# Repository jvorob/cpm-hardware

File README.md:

# cpm-hardware

This repo contains the design files for the custom PCB used in my Cathodic Protection Monitoring project.
These were developed in KiCad 8.
(see [main repo](https://github.com/jvorob/cpm-firmware) for more details)

`cpm_proj/` Contains the mk1 board used as of 2024.06.16, a 100x100mm 2-layer PCB.

`cpm_mk2/` is the start of a planned second version, if I get around to miniaturizing and deploying it.

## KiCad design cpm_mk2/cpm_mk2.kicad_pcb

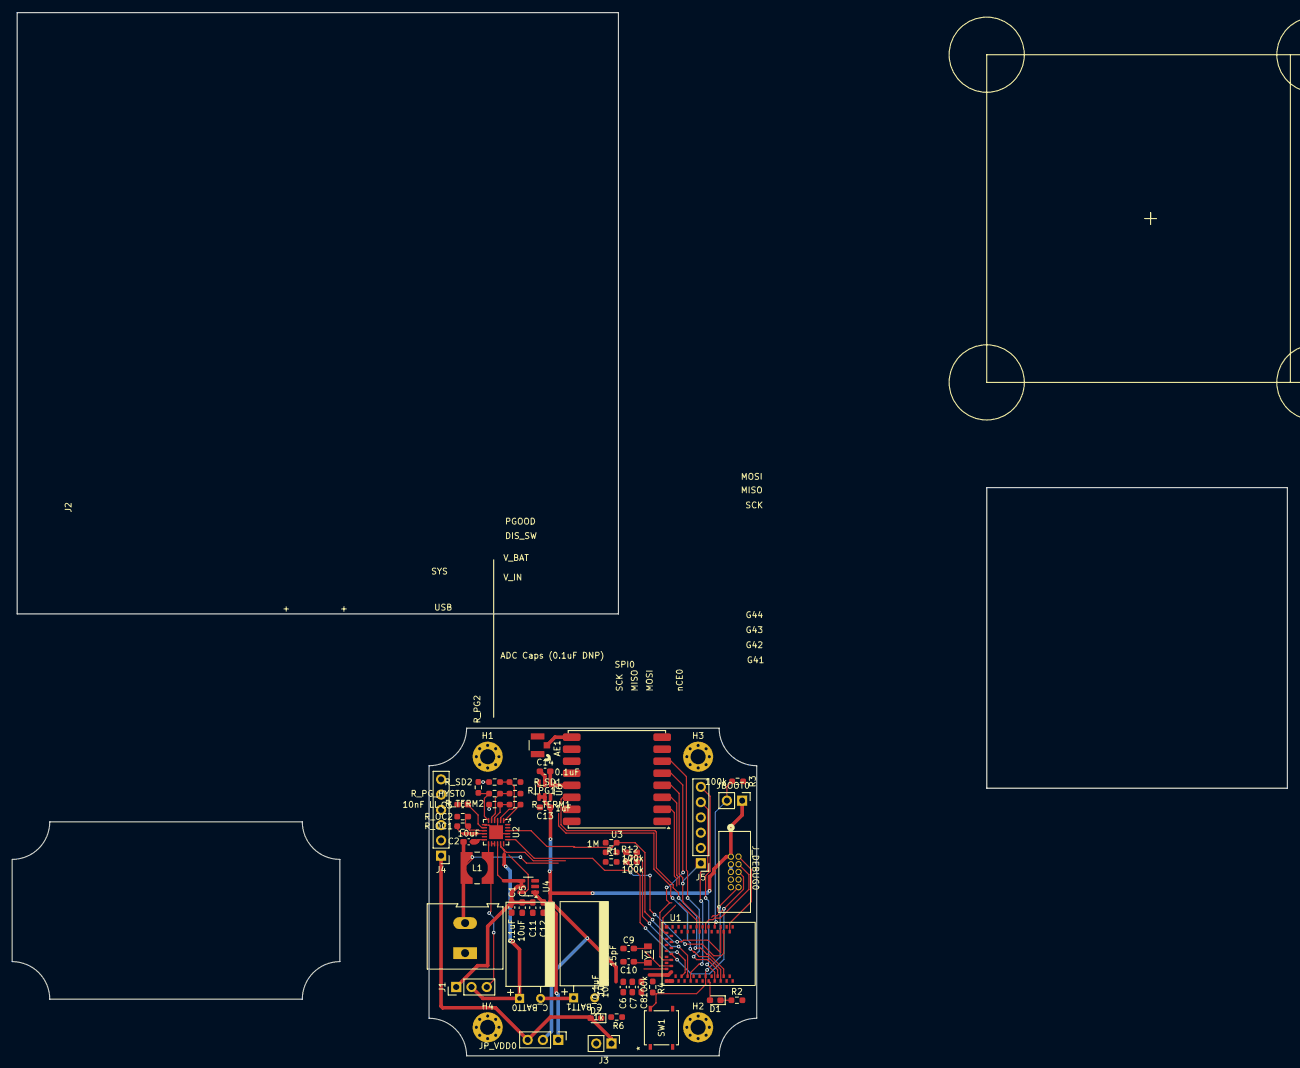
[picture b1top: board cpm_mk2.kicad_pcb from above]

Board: 2 copper layers, 54.5 x 54.5 mm, 56 parts (0 on the bottom side), 42 nets.

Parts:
AE1: Antenna_Shield; CONN1_CONUFL_TEC
C1, C6, C12, C14: 0.1uF; C_0603_1608Metric_Pad1.08x0.95mm_HandSolder
C2, C5, C8: 10uF; C_0603_1608Metric_Pad1.08x0.95mm_HandSolder
C3: 10nF LL; C_0603_1608Metric_Pad1.08x0.95mm_HandSolder
C7, C11, C13: 1uF; C_0603_1608Metric_Pad1.08x0.95mm_HandSolder
C9, C10: 15pF; C_0603_1608Metric_Pad1.08x0.95mm_HandSolder
C15, C22: 1nF; C_0603_1608Metric_Pad1.08x0.95mm_HandSolder
C_BATT0, C_BATT1: 1F 2.7V; DGH105Q2R7
D1, D2: LED; LED_0603_1608Metric_Pad1.05x0.95mm_HandSolder
H1, H2, H3, H4: MountingHole_Pad; MountingHole_2.5mm_Pad_Via
J1: Conn_01x03_Pin; PinHeader_1x03_P2.54mm_Vertical
J2: Screw_Terminal_01x02; TerminalBlock_Altech_AK300-2_P5.00mm
J3: Conn_01x02_Pin; PinHeader_1x02_P2.54mm_Vertical
J4, J5: Conn_01x06_Pin; PinHeader_1x06_P2.54mm_Vertical
JBOOT0: Conn_01x02_Pin; PinHeader_1x02_P2.54mm_Vertical
JP_VDD0: Conn_01x03_Pin; PinHeader_1x03_P2.54mm_Vertical
J_DEBUG0: Conn_02x05_Odd_Even; CONN_3220-10-0100-00_CNC
L1: 22uH; IND_4818-WE-TPC_WRE
R1: 1M; R_0603_1608Metric_Pad0.98x0.95mm_HandSolder
R2, R6: 1k; R_0603_1608Metric_Pad0.98x0.95mm_HandSolder
R3, R4, R11, R12: 100k; R_0603_1608Metric_Pad0.98x0.95mm_HandSolder
R_OC1, R_OC2: 10M; R_0603_1608Metric_Pad0.98x0.95mm_HandSolder
R_PG1: 5.6M; R_0603_1608Metric_Pad0.98x0.95mm_HandSolder
R_PG2: 4.7M; R_0603_1608Metric_Pad0.98x0.95mm_HandSolder
R_PG_HYST0: 470k; R_0603_1608Metric_Pad0.98x0.95mm_HandSolder
R_SD1, R_SD2: 4.7M; R_0603_1608Metric_Pad0.98x0.95mm_HandSolder
R_TERM1: 5.6M; R_0603_1608Metric_Pad0.98x0.95mm_HandSolder
R_TERM2: 4.7M; R_0603_1608Metric_Pad0.98x0.95mm_HandSolder
SW1: RESET; SMT_FS_PTS526
U1: Sparkfun Artemis
U2: ADP5091; LFCSP-24-1EP_4x4mm_P0.5mm_EP2.3x2.3mm
U3: RFM95W-915S2; HOPERF_RFM9XW_SMD
U4, U6: TPS22860; SOT-23-6
Y1: 32.768kHz; XTAL_ECS-31B_ECS

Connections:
/SPI0.MISO: J5.2, U1.23 (GPIO6), U3.2 (MISO)
/SPI0.MOSI: J5.3, U1.13 (GPIO7), U3.3 (MOSI)
/SPI0.SCK: J5.1, U1.12 (GPIO5), U3.4 (SCK)
/SPI0.nCE0: J5.4, U1.32 (GPIO11), U3.5 (NSS)
/VADP_{IN}: C2.1, J2.2, J4.3, L1.2, R11.1, R_OC1.1, U2.10 (VIN)
/VADP_{OUT}: C1.1, C5.1, C11.1, J1.1, U2.16 (SYS), U4.4 (V_{IN}), U4.5 (V_{BIAS})
/VIN_{3V3}: D2.2 (A), J3.1, J4.1, JP_VDD0.3
/artemis/ADC0/TRIG0/CMPIN0: C15.2, R11.2, U1.42 (GPIO16)
/artemis/ADC3: C22.2, R12.2, U1.44 (GPIO31)
/artemis/BOOT: JBOOT0.2, R3.1, U1.7 (GPIO47/BOOT)
/artemis/DIS_SW: R1.1, U1.5 (GPIO40), U2.22 (DIS_SW)
/artemis/LED: D1.2 (A), U1.51 (GPIO0)
/artemis/LORA_EN: U1.55 (GPIO36), U6.6 (ON)
/artemis/LORA_RST: U1.54 (GPIO3), U3.6 (RESET)
/artemis/LORA_T/RXDONE: U1.56 (GPIO38), U3.14 (DIO0)
/artemis/MISC_GPIO_0: J5.5, U1.45 (GPIO41)
/artemis/MISC_GPIO_1: J5.6, U1.53 (GPIO42)
/artemis/PWR_GOOD: U1.4 (GPIO39), U2.19 (PGOOD), U4.6 (ON)
/artemis/SWDCK: J_DEBUG0.2, U1.2 (GPIO20/SWDCK)
/artemis/SWDIO: J_DEBUG0.4, U1.10 (GPIO21/SWDIO)
/artemis/SWO: J_DEBUG0.6, U1.30 (GPIO33)
/artemis/nRESET: J_DEBUG0.10, R4.2, SW1.1, SW1.2, U1.50 (nRESET)
/lora/V33_{LORA}: C14.1, U3.13 (3.3V), U6.1 (V_{OUT})
/power/SW: J1.3, L1.1, U2.13 (SW)
/power/V_BAT: C_BATT0.1 (+), J1.2, R12.1, U2.17 (BAT)
GND: AE1.2 (Shield), C1.2, C2.2, C3.1, C5.2, C6.2, C7.2, C8.2, C9.2, C10.2, C11.2, C12.2, C13.2, C14.2, C15.1, C22.1, C_BATT1.2 (-), H1.1, H2.1, H3.1, H4.1, J2.1, J3.2, J4.4, J4.5, J4.6, J_DEBUG0.3, J_DEBUG0.5, J_DEBUG0.9, R1.2, R2.2, R3.2, R6.2, R_OC2.2, R_PG2.2, R_SD2.2, R_TERM2.2, SW1.3 (K), SW1.4 (A), U1.1 (GND), U1.22 (GND), U1.38 (GND), U1.39 (GND), U1.47 (GND), U1.59 (GND), U2.3 (SETBK), U2.7 (AGND), U2.12 (PGND), U2.20 (VID), U2.21 (MINOP), U2.23 (REG_D1), U2.24 (REG_D0), U2.25 (AGND), U3.1 (GND), U3.8 (GND), U3.10 (GND), U4.2 (GND), U6.2 (GND)
unnamed: AE1.1 (A), U3.9 (ANT)
unnamed: C_BATT0.2 (-), C_BATT1.1 (+)
unnamed: D1.1 (K), R2.1
unnamed: D2.1 (K), R6.1
unnamed: C12.1, JP_VDD0.1, U4.1 (V_{OUT})
unnamed: C10.1, U1.35 (XI), Y1.1
unnamed: C9.1, U1.34 (XO), Y1.2
unnamed: C3.2, U2.8 (CBP)
unnamed: R_OC1.2, R_OC2.1, U2.9 (MPPT)
unnamed: R_PG1.1, R_SD1.1, R_TERM1.1, U2.1 (REF)
unnamed: U2.14 (REG_OUT), U2.15 (REG_FB)
unnamed: R_PG2.1, R_PG_HYST0.2, U2.6 (SETHYST)
unnamed: R_PG1.2, R_PG_HYST0.1, U2.5 (SETPG)
unnamed: R_SD1.2, R_SD2.1, U2.2 (SETSD)
unnamed: R_TERM1.2, R_TERM2.1, U2.4 (TERM)
VDD: C6.1, C7.1, C8.1, C13.1, J4.2, JBOOT0.1, JP_VDD0.2, J_DEBUG0.1, R4.1, U1.36 (VDD), U1.37 (VDD), U6.4 (V_{IN}), U6.5 (V_{BIAS})

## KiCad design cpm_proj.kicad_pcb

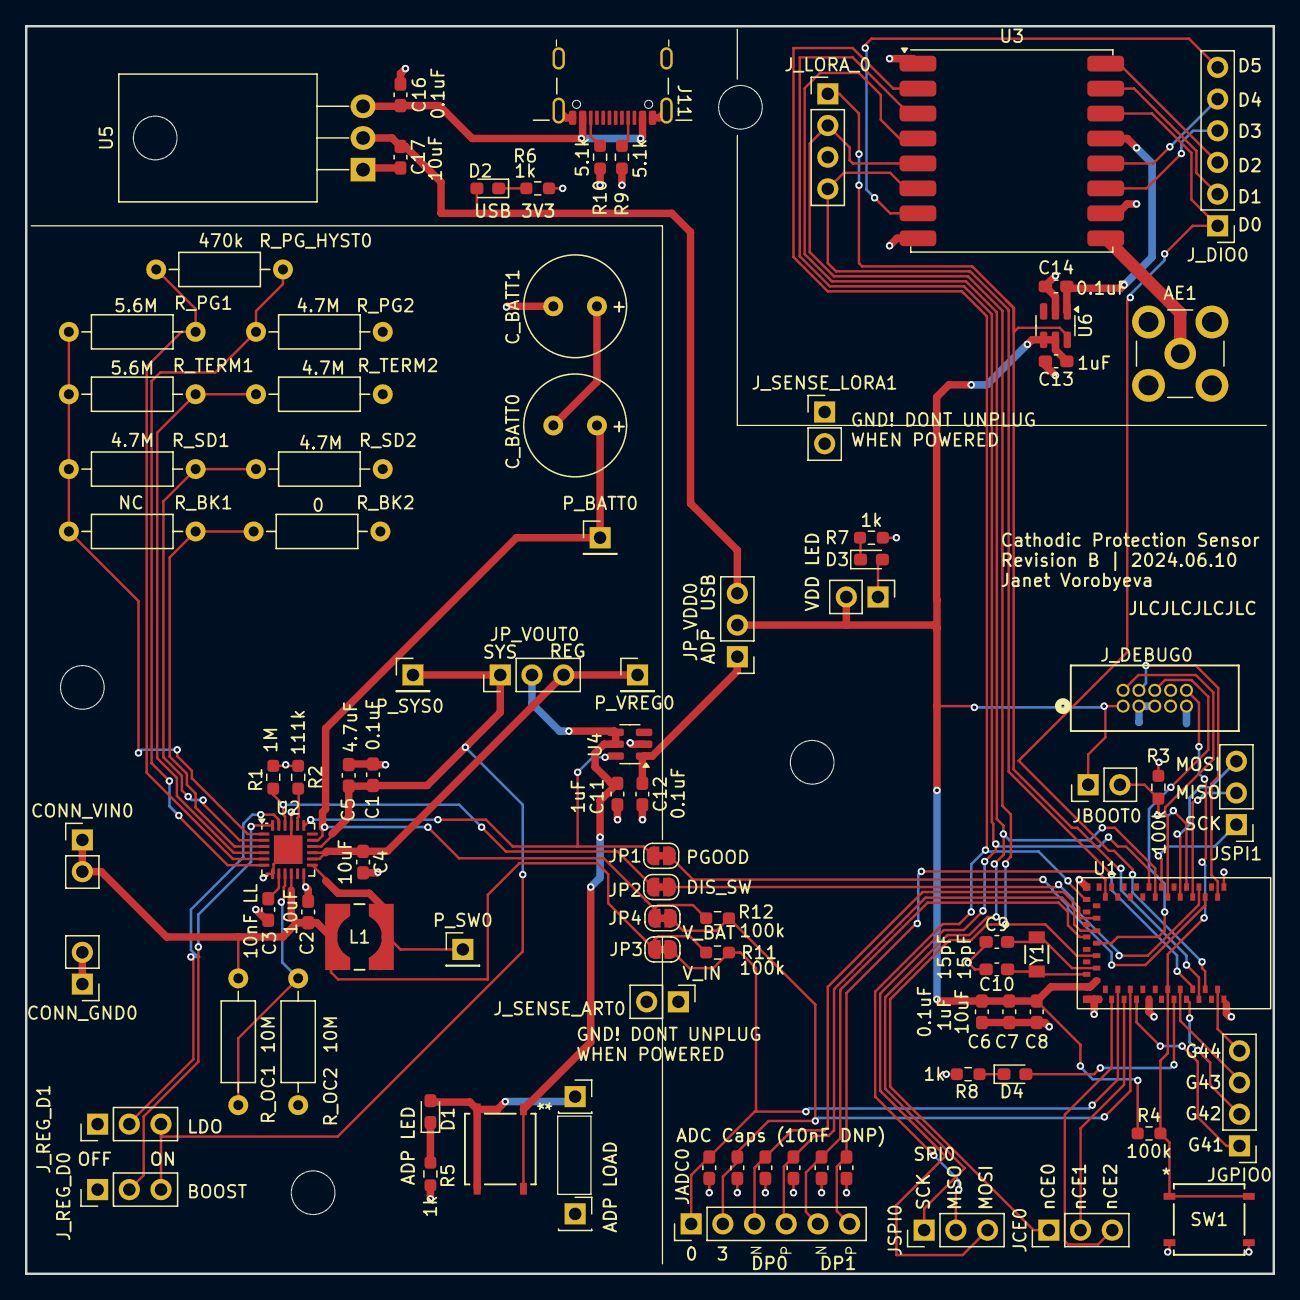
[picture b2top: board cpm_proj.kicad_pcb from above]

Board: 2 copper layers, 100.0 x 100.0 mm, 95 parts (0 on the bottom side), 74 nets.

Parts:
AE1: Antenna_Shield; SMB_Jack_Vertical_RF2
C1, C6, C12, C14, C16: 0.1uF; C_0603_1608Metric_Pad1.08x0.95mm_HandSolder
C2, C4, C8, C17: 10uF; C_0603_1608Metric_Pad1.08x0.95mm_HandSolder
C3: 10nF LL; C_0603_1608Metric_Pad1.08x0.95mm_HandSolder
C5: 4.7uF; C_0603_1608Metric_Pad1.08x0.95mm_HandSolder
C7, C11, C13: 1uF; C_0603_1608Metric_Pad1.08x0.95mm_HandSolder
C9, C10: 15pF; C_0603_1608Metric_Pad1.08x0.95mm_HandSolder
C15, C18, C19, C20, C21, C22: 1nF; C_0603_1608Metric_Pad1.08x0.95mm_HandSolder
CONN_GND0: Conn_01x02_Pin; PinHeader_1x02_P2.54mm_Vertical
CONN_VIN0: Conn_01x02_Pin; PinHeader_1x02_P2.54mm_Vertical
C_BATT0, C_BATT1: 1F 2.7V; C_Radial_D8.0mm_H11.5mm_P3.50mm
D1, D2, D3, D4: LED; LED_0603_1608Metric_Pad1.05x0.95mm_HandSolder
H1, H2, H3, H4: MountingHole; MountingHole_3.5mm
J11: USB_C_Receptacle_USB2.0; USB4105-GF-A
JADC0: Conn_01x06_Pin; PinHeader_1x06_P2.54mm_Vertical
JBOOT0: Conn_01x02_Pin; PinHeader_1x02_P2.54mm_Vertical
JCE0: Conn_01x03_Pin; PinHeader_1x03_P2.54mm_Vertical
JGPIO0: Conn_01x04_Pin; PinHeader_1x04_P2.54mm_Vertical
JP1, JP2, JP3, JP4: SolderJumper_2_Bridged; SolderJumper-2_P1.3mm_Bridged_RoundedPad1.0x1.5mm
JP_VDD0: Conn_01x03_Pin; PinHeader_1x03_P2.54mm_Vertical
JP_VOUT0: Conn_01x03_Pin; PinHeader_1x03_P2.54mm_Vertical
JSPI0, JSPI1: Conn_01x03_Pin; PinHeader_1x03_P2.54mm_Vertical
J_DEBUG0: Conn_02x05_Odd_Even; CONN_3220-10-0100-00_CNC
J_DIO0: Conn_01x06_Pin; PinHeader_1x06_P2.54mm_Vertical
J_LOAD0, J_LOAD1: Conn_01x01_Socket; PinSocket_1x01_P2.54mm_Vertical
J_LORA_0: Conn_01x04_Pin; PinHeader_1x04_P2.54mm_Vertical
J_REG_D0, J_REG_D1: Conn_01x03_Pin; PinHeader_1x03_P2.54mm_Vertical
J_SENSE_ART0: Conn_01x02_Pin; PinHeader_1x02_P2.54mm_Vertical
J_SENSE_LORA1: Conn_01x02_Pin; PinHeader_1x02_P2.54mm_Vertical
J_VDD_LED0: Conn_01x02_Pin; PinHeader_1x02_P2.54mm_Vertical
L1: 22uH; IND_4818-WE-TPC_WRE
P_BATT0: Conn_01x01_Pin; PinHeader_1x01_P2.54mm_Vertical
P_SW0: Conn_01x01_Pin; PinHeader_1x01_P2.54mm_Vertical
P_SYS0: Conn_01x01_Socket; PinHeader_1x01_P2.54mm_Vertical
P_VREG0: Conn_01x01_Socket; PinHeader_1x01_P2.54mm_Vertical
R1: 1M; R_0603_1608Metric_Pad0.98x0.95mm_HandSolder
R2: 111k; R_0603_1608Metric_Pad0.98x0.95mm_HandSolder
R3, R4, R11, R12: 100k; R_0603_1608Metric_Pad0.98x0.95mm_HandSolder
R5, R6, R7, R8: 1k; R_0603_1608Metric_Pad0.98x0.95mm_HandSolder
R9, R10: 5.1k; R_0603_1608Metric_Pad0.98x0.95mm_HandSolder
R_BK1: NC; R_Axial_DIN0207_L6.3mm_D2.5mm_P10.16mm_Horizontal
R_BK2: 0; R_Axial_DIN0207_L6.3mm_D2.5mm_P10.16mm_Horizontal
R_OC1, R_OC2: 10M; R_Axial_DIN0207_L6.3mm_D2.5mm_P10.16mm_Horizontal
R_PG1: 5.6M; R_Axial_DIN0207_L6.3mm_D2.5mm_P10.16mm_Horizontal
R_PG2: 4.7M; R_Axial_DIN0207_L6.3mm_D2.5mm_P10.16mm_Horizontal
R_PG_HYST0: 470k; R_Axial_DIN0207_L6.3mm_D2.5mm_P10.16mm_Horizontal
R_SD1, R_SD2: 4.7M; R_Axial_DIN0207_L6.3mm_D2.5mm_P10.16mm_Horizontal
R_TERM1: 5.6M; R_Axial_DIN0207_L6.3mm_D2.5mm_P10.16mm_Horizontal
R_TERM2: 4.7M; R_Axial_DIN0207_L6.3mm_D2.5mm_P10.16mm_Horizontal
SW1: RESET; SMT_FS_PTS526
SW_ADP_LED0: ADP_LED; SMT_FS_PTS526
U1: Sparkfun Artemis
U2: ADP5091; LFCSP-24-1EP_4x4mm_P0.5mm_EP2.3x2.3mm
U3: RFM95W-915S2; HOPERF_RFM9XW_SMD
U4, U6: TPS22860; SOT-23-6
U5: LD1117AV33_TO220; TO-220-3_Horizontal_TabDown
Y1: 32.768kHz; XTAL_ECS-31B_ECS

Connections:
/SPI0.MISO: JSPI0.2, U1.23 (GPIO6), U3.2 (MISO)
/SPI0.MOSI: JSPI0.3, U1.13 (GPIO7), U3.3 (MOSI)
/SPI0.SCK: JSPI0.1, U1.12 (GPIO5), U3.4 (SCK)
/SPI0.nCE0: JCE0.1, J_LORA_0.2, U1.32 (GPIO11), U3.5 (NSS)
/SPI0.nCE1: JCE0.2, U1.43 (GPIO17)
/SPI0.nCE2: JCE0.3, U1.41 (GPIO18)
/VADP_{IN}: C2.1, CONN_VIN0.1, CONN_VIN0.2, JP3.1 (A), L1.2, R11.1, R_OC1.1, U2.10 (VIN)
/VADP_{OUT}: C11.1, JP_VOUT0.2, SW_ADP_LED0.1, SW_ADP_LED0.2, U4.4 (V_{IN}), U4.5 (V_{BIAS})
/VUSB_{3V3}: C17.1, D2.2 (A), JP_VDD0.3, U5.2 (VO)
/VUSB_{5V}: C16.1, J11.A4/B9 (VBUS), J11.A9/B4 (VBUS), U5.3 (VI)
/artemis/ADC0/TRIG0/CMPIN0: C15.2, JADC0.1, JP3.2 (B), R11.2, U1.42 (GPIO16)
/artemis/ADC3: C22.2, JADC0.2, JP4.2 (B), R12.2, U1.44 (GPIO31)
/artemis/ADC_DP0_{N}: C18.2, JADC0.3, U1.26 (GPIO12)
/artemis/ADC_DP0_{P}: C19.2, JADC0.4, U1.28 (GPIO13)
/artemis/ADC_DP1_{N}: C20.2, JADC0.5, U1.29 (GPIO15)
/artemis/ADC_DP1_{P}: C21.2, JADC0.6, U1.20 (GPIO14)
/artemis/BOOT: JBOOT0.2, R3.1, U1.7 (GPIO47/BOOT)
/artemis/DIS_SW: JP2.2 (B), U1.5 (GPIO40)
/artemis/GND_{ARTEMIS}: C6.2, C7.2, C8.2, C9.2, C10.2, C15.1, C18.1, C19.1, C20.1, C21.1, C22.1, J_DEBUG0.3, J_DEBUG0.5, J_DEBUG0.9, J_SENSE_ART0.1, R3.2, R8.2, SW1.3 (K), SW1.4 (A), U1.1 (GND), U1.22 (GND), U1.38 (GND), U1.39 (GND), U1.47 (GND), U1.59 (GND)
/artemis/LED: D4.2 (A), U1.51 (GPIO0)
/artemis/LORA_EN: J_LORA_0.1, U1.55 (GPIO36), U6.6 (ON)
/artemis/LORA_T/RXDONE: J_DIO0.1, U1.56 (GPIO38), U3.14 (DIO0)
/artemis/LORA_nRST: J_LORA_0.4, U1.54 (GPIO3), U3.6 (nRESET)
/artemis/MISC_GPIO_0: JGPIO0.1, U1.45 (GPIO41)
/artemis/MISC_GPIO_1: JGPIO0.2, U1.53 (GPIO42)
/artemis/MISC_GPIO_2: JGPIO0.3, U1.52 (GPIO43)
/artemis/MISC_GPIO_3: JGPIO0.4, U1.58 (GPIO44)
/artemis/PWR_GOOD: JP1.2 (B), U1.4 (GPIO39)
/artemis/SPI1.MISO: JSPI1.2, U1.6 (GPIO9)
/artemis/SPI1.MOSI: JSPI1.3, U1.8 (GPIO10)
/artemis/SPI1.SCK: JSPI1.1, U1.11 (GPIO8)
/artemis/SWDCK: J_DEBUG0.4, U1.2 (GPIO20/SWDCK)
/artemis/SWDIO: J_DEBUG0.2, U1.10 (GPIO21/SWDIO)
/artemis/SWO: J_DEBUG0.6, U1.30 (GPIO33)
/artemis/nRESET: J_DEBUG0.10, R4.2, SW1.1, SW1.2, U1.50 (nRESET)
/lora/GND_LORA_SENSE: AE1.2 (Shield), C13.2, C14.2, J_SENSE_LORA1.1, U3.1 (GND), U3.8 (GND), U3.10 (GND), U6.2 (GND)
/lora/V33_{LORA}: C14.1, U3.13 (3.3V), U6.1 (V_{OUT})
/power/BAT: C_BATT0.1 (+), JP4.1 (A), P_BATT0.1, R12.1, U2.17 (BAT)
/power/DIS_SW: JP2.1 (A), R1.1, U2.22 (DIS_SW)
/power/PGOOD: JP1.1 (A), U2.19 (PGOOD), U4.6 (ON)
/power/REG_D0: J_REG_D0.2, U2.24 (REG_D0)
/power/REG_D1: J_REG_D1.2, U2.23 (REG_D1)
/power/SW: L1.1, P_SW0.1, U2.13 (SW)
/power/VID: R2.1, U2.20 (VID)
/power/V_REG: C4.1, JP_VOUT0.3, P_VREG0.1, U2.14 (REG_OUT), U2.15 (REG_FB)
/power/V_SYS: C1.1, C5.1, JP_VOUT0.1, J_REG_D0.3, J_REG_D1.3, P_SYS0.1, U2.16 (SYS)
GND: C1.2, C2.2, C3.1, C4.2, C5.2, C11.2, C12.2, C16.2, C17.2, CONN_GND0.1, CONN_GND0.2, C_BATT1.2 (-), J11.A1/B12 (GND), J11.A12/B1 (GND), J11.S1 (SHIELD), J_LOAD1.1, J_REG_D0.1, J_REG_D1.1, J_SENSE_ART0.2, J_SENSE_LORA1.2, R1.2, R2.2, R5.2, R6.2, R7.2, R9.2, R10.2, R_BK2.2, R_OC2.2, R_PG2.2, R_SD2.2, R_TERM2.2, U2.7 (AGND), U2.12 (PGND), U2.21 (MINOP), U2.25 (AGND), U4.2 (GND), U5.1 (GND)
unnamed: AE1.1 (A), U3.9 (ANT)
unnamed: C_BATT0.2 (-), C_BATT1.1 (+)
unnamed: D1.2 (A), J_LOAD0.1, SW_ADP_LED0.3 (K), SW_ADP_LED0.4 (A)
unnamed: D1.1 (K), R5.1
unnamed: D2.1 (K), R6.1
unnamed: D3.2 (A), J_VDD_LED0.1
unnamed: D3.1 (K), R7.1
unnamed: D4.1 (K), R8.1
unnamed: J11.A5 (CC1), R9.1
unnamed: J11.B5 (CC2), R10.1
unnamed: C12.1, JP_VDD0.1, U4.1 (V_{OUT})
unnamed: J_DIO0.2, U3.15 (DIO1)
unnamed: J_DIO0.3, U3.16 (DIO2)
unnamed: J_DIO0.4, U3.11 (DIO3)
unnamed: J_DIO0.5, U3.12 (DIO4)
unnamed: J_DIO0.6, U3.7 (DIO5)
unnamed: C10.1, U1.35 (XI), Y1.1
unnamed: C9.1, U1.34 (XO), Y1.2
unnamed: C3.2, U2.8 (CBP)
unnamed: R_OC1.2, R_OC2.1, U2.9 (MPPT)
unnamed: R_BK1.1, R_PG1.1, R_SD1.1, R_TERM1.1, U2.1 (REF)
unnamed: R_BK1.2, R_BK2.1, U2.3 (SETBK)
unnamed: R_PG2.1, R_PG_HYST0.2, U2.6 (SETHYST)
unnamed: R_PG1.2, R_PG_HYST0.1, U2.5 (SETPG)
unnamed: R_SD1.2, R_SD2.1, U2.2 (SETSD)
unnamed: R_TERM1.2, R_TERM2.1, U2.4 (TERM)
VDD: C6.1, C7.1, C8.1, C13.1, JBOOT0.1, JP_VDD0.2, J_DEBUG0.1, J_VDD_LED0.2, R4.1, U1.36 (VDD), U1.37 (VDD), U6.4 (V_{IN}), U6.5 (V_{BIAS})

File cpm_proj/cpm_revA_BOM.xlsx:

Reference | Type | Value | Datasheet | Footprint | Qty | In Stock? | Order | DNP |  | PN | Digikey PN
C9,C10 | Passive – Capacitor | 15pF | ~ | Capacitor_SMD:C_0603_1608Metric_Pad1.08x0.95mm_HandSolder | 2 | ~30
C15,C18,C19,C20,C21,C22 | Passive – Capacitor | 1nF | ~ | Capacitor_SMD:C_0603_1608Metric_Pad1.08x0.95mm_HandSolder | 6 | ~30 |  | DNP
C1,C6,C12,C14,C16 | Passive – Capacitor | 0.1uF | ~ | Capacitor_SMD:C_0603_1608Metric_Pad1.08x0.95mm_HandSolder | 5 | ~20
C7,C11,C13 | Passive – Capacitor | 1uF | ~ | Capacitor_SMD:C_0603_1608Metric_Pad1.08x0.95mm_HandSolder | 3 | 30
C5 | Passive – Capacitor | 4.7uF | ~ | Capacitor_SMD:C_0603_1608Metric_Pad1.08x0.95mm_HandSolder | 1 | 0 | 50 |  | Jelly | C1608X5R1E475K080AC | 445-9050-1-ND
C2,C4,C8,C17 | Passive – Capacitor | 10uF | ~ | Capacitor_SMD:C_0603_1608Metric_Pad1.08x0.95mm_HandSolder | 4 | ~5
R11,R12,R3,R4 | Passive – Resistor | 100k | ~ | Resistor_SMD:R_0603_1608Metric_Pad0.98x0.95mm_HandSolder | 4 | ~20
R2 | Passive – Resistor | 111k | ~ | Resistor_SMD:R_0603_1608Metric_Pad0.98x0.95mm_HandSolder | 1 | ~20
R5,R6,R7,R8 | Passive – Resistor | 1k | ~ | Resistor_SMD:R_0603_1608Metric_Pad0.98x0.95mm_HandSolder | 4 | ~20 | 1000 |  | Jelly | RMCF0603FG1K00 | RMCF0603FG1K00CT-ND
R9,R10 | Passive – Resistor | 5.1k | ~ | Resistor_SMD:R_0603_1608Metric_Pad0.98x0.95mm_HandSolder | 2 | ~20
R1 | Passive – Resistor | 1M | ~ | Resistor_SMD:R_0603_1608Metric_Pad0.98x0.95mm_HandSolder | 1 | 0 | 50? |  | Jelly | RMCF0603FG1M00 | RMCF0603FG1M00CT-ND
R_OC1,R_OC2 | Passive – Resistor | 10M | ~ | Resistor_THT:R_Axial_DIN0207_L6.3mm_D2.5mm_P10.16mm_Horizontal | 2 | 8 | 0
R_PG1,R_TERM1 | Passive – Resistor | 5.6M | ~ | Resistor_THT:R_Axial_DIN0207_L6.3mm_D2.5mm_P10.16mm_Horizontal | 2 | 0 | 10 |  |  | CF14JT5M60 | CF14JT5M60CT-ND
R_PG2,R_SD1,R_SD2,R_TERM2 | Passive – Resistor | 4.7M | ~ | Resistor_THT:R_Axial_DIN0207_L6.3mm_D2.5mm_P10.16mm_Horizontal | 4 | 10 | 0
R_PG_HYST0 | Passive – Resistor | 470k | ~ | Resistor_THT:R_Axial_DIN0207_L6.3mm_D2.5mm_P10.16mm_Horizontal | 1 | 5 | 0
R_BK1 | N/A | NC | ~ | Resistor_THT:R_Axial_DIN0207_L6.3mm_D2.5mm_P10.16mm_Horizontal | 1 | N/A |  | DNP
R_BK2 | N/A | 0 | ~ | Resistor_THT:R_Axial_DIN0207_L6.3mm_D2.5mm_P10.16mm_Horizontal | 1 | N/A
C3 | Passive – Special | 10nF LL | https://www.digikey.com/en/products/detail/murata-electronic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 | Capacitor_SMD:C_0603_1608Metric_Pad1.08x0.95mm_HandSolder | 1 | 0 | 10 |  |  | GRT1885C1E103JA02J | 490-GRT1885C1E103JA02JCT-ND
C_BATT0,C_BATT1 | Supercapacitor | 1F 2.7V | https://www.digikey.com/en/products/detail/cornell-dubilier-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 | Capacitor_THT:C_Radial_D8.0mm_H11.5mm_P3.50mm | 2 | 2 | 10 |  |  | DGH105Q2R7 | 338-DGH105Q2R7-ND
D1,D2,D3,D4 | Led | LED GN? | ~ | LED_SMD:LED_0603_1608Metric_Pad1.05x0.95mm_HandSolder | 4 | 0 | 20? |  | Jelly | SML-D12P8WT86 | 846-SML-D12P8WT86CT-ND
SW1, SW_ADP_LED0 | Switch | PTS526 Switch | https://www.digikey.com/en/products/detail/c-k/PTS526-SK15-S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 | 0JV_CPM_Footprints:SMT_FS_PTS526 | 2 |  | 25 |  | Jelly | PTS526 SK15 SMTR2 LFS | CKN12221-1-ND
U1 | IC | Sparkfun Artemis | https://cdn.sparkfun.com/assets/learn_tutorials/9/0/9/Artemi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 | 0JV_CPM_Footprints:Sparkfun Artemis | 1 | 0 | 10? |  | Restock | WRL-15484 | 1568-WRL-15484CT-ND | 30c cheaper on sparkfun? |  | https://www.sparkfun.com/products/15484
U2 | IC | ADP5091 | https://www.analog.com/media/en/technical-documentation/data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 | Package_CSP:LFCSP-24-1EP_4x4mm_P0.5mm_EP2.3x2.3mm | 1 | ??? | 2? |  |  | ADP5091ACPZ-1-R7 | 505-ADP5091ACPZ-1-R7CT-ND
U3 | IC | RFM95W-915S2 | https://www.hoperf.com/data/upload/portal/20181127/5bfcbea20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 | RF_Module:HOPERF_RFM9XW_SMD | 1 | ~2 | 0
U4,U6 | IC | TPS22860 | https://www.ti.com/lit/ds/symlink/tps22860.pdf | Package_TO_SOT_SMD:SOT-23-6 | 2 | 0 | 5? |  |  | TPS22860DBVR | 296-43982-1-ND
U5 | IC | LD1117AV33_TO220 | https://www.st.com/content/ccc/resource/technical/document/d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 | Package_TO_SOT_THT:TO-220-3_Horizontal_TabDown | 1 | 1 | 0
Y1 | Crystal | 32.768kHz | https://www.digikey.com/en/products/detail/ecs-inc/ECS-327-1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 | 0JV_CPM_Footprints:XTAL_ECS-31B_ECS | 1 | 0 | 10 |  |  | ECS-.327-12.5-34B-TR | XC1617CT-ND
L1 | Inductor | 22uH | https://www.digikey.com/en/products/detail/w%C3%BCrth-elektr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 | 0JV_CPM_Footprints:IND_4818-WE-TPC_WRE | 1 | 0 | 10? |  |  | 744042220 | 732-3657-1-ND
J11 | Connector | USB_C_Receptacle_USB2.0 | https://www.digikey.com/en/products/detail/gct/USB4105-GF-A/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 | 0JV_CPM_Footprints:USB4105-GF-A | 1 | 0 | 10 |  | Jelly | USB4105-GF-A | 2073-USB4105-GF-ACT-ND
J_DEBUG0 | Connector | Conn_02x05_Odd_Even | https://www.digikey.com/en/products/detail/cnc-tech/3220-10-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 | 0JV_CPM_Footprints:CONN_3220-10-0100-00_CNC | 1 | 1 | 0 |  |  | 3220-10-0100-00 | 1175-1627-ND
AE1 | Connector | Antenna_Shield | https://app.adam-tech.com/products/download/data_sheet/21910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 | 0JV_CPM_Footprints:SMB_Jack_Vertical_RF2 | 1 | 1 | 0 |  |  |  | 2057-RF2-04A-T-00-50-G-ND
JADC0,J_DIO0 | JB Connector | Conn_01x06_Pin | ~ | Connector_PinHeader_2.54mm:PinHeader_1x06_P2.54mm_Vertical | 2 | 1
JCE0,JP_VDD0,JP_VOUT0,JSPI0,JSPI1,J_REG_D0,J_REG_D1 | JB Connector | Conn_01x03_Pin | ~ | Connector_PinHeader_2.54mm:PinHeader_1x03_P2.54mm_Vertical | 7 | 1
JGPIO0,J_LORA_0 | JB Connector | Conn_01x04_Pin | ~ | Connector_PinHeader_2.54mm:PinHeader_1x04_P2.54mm_Vertical | 2 | 1
J_LOAD0,J_LOAD1,P_SYS0,P_VREG0 | JB Connector | Conn_01x01_Socket | ~ | -- mixed values -- | 4 | 1
P_BATT0,P_SW0 | JB Connector | Conn_01x01_Pin | ~ | Connector_PinHeader_2.54mm:PinHeader_1x01_P2.54mm_Vertical | 2 | 1
CONN_GND0,CONN_VIN0,JBOOT0,J_SENSE_ART0,J_SENSE_LORA1,J_VDD_LED0 | JB Connector | Conn_01x02_Pin | ~ | Connector_PinHeader_2.54mm:PinHeader_1x02_P2.54mm_Vertical | 6 | 1
 |  | Big resistor kit? (100k-10Mohm, 0603) |  |  |  |  |  |  | (resistor kit) | KIT-RMCF0603JT-14
 |  | MEGOHM Resistors: | ( for kit-making |  |  | in stock | order?
 |  | 1 |  |  |  | 10
 |  | 1.5 |  |  |  | 0 | 10 |  | Misc 1-10Mohm THT resistors (filling gaps in our current stock)
 |  | 2.2 |  |  |  | 10
 |  | 3.3 |  |  |  | 0 | 10
 |  | 4.7 |  |  |  | 10
 |  | 6.8 |  |  |  |  | 10
 |  | 10 |  |  |  | 10

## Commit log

2024-05-20 rev A (first pcb order)
2024-06-11 Revision B
    Fixed SWDIO/SWDCK
    Relabeled ADC Caps to 10nF
    Relabelled LORA reset line to active low
    Minor silkscreen tweaks
2024-06-15 Removed bonus JLCJLC text
2024-06-15 Added backups to gitignore
2024-06-16 Moved everything one directory deeper
2024-06-16 Added cpm_mk2 repo
2024-06-16 readme
